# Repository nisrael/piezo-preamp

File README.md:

# piezo-preamp

This is a piezo preamp with a gain boost and a variable high and low pass filter.
It is a modification of the DIY ilski PB-1 (https://breaksberlin.wordpress.com/2015/11/07/diy-piezo-preamp-with-hi-pass-filter/).

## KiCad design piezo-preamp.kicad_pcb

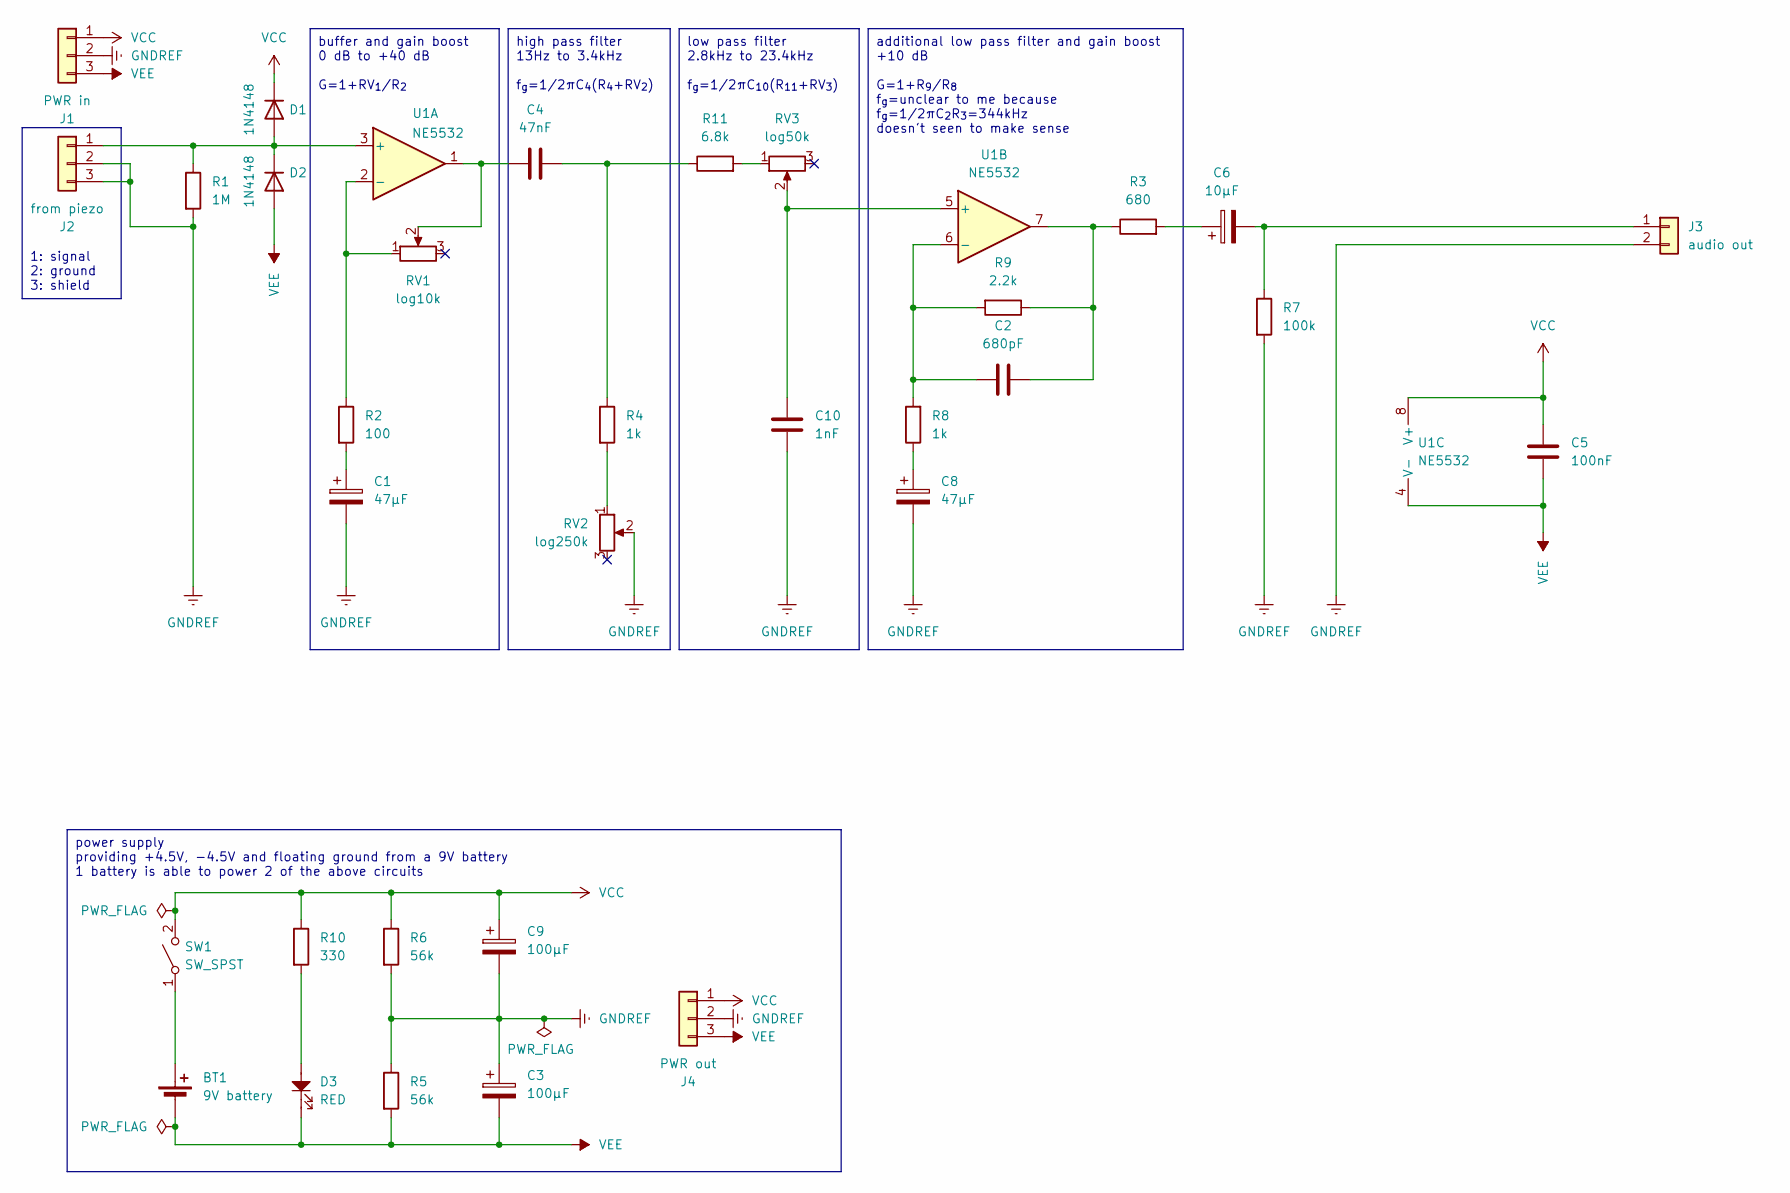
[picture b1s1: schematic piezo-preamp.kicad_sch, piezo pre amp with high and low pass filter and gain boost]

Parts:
BT1: 9V battery; PinHeader_1x02_P2.54mm_Vertical
C1, C8: 47µF; CP_Radial_D5.0mm_P2.50mm
C2: 680pF; CP_Radial_D5.0mm_P2.50mm
C3, C9: 100µF; CP_Radial_D5.0mm_P2.50mm
C4: 47nF; CP_Radial_D5.0mm_P2.50mm
C5: 100nF; CP_Radial_D5.0mm_P2.50mm
C6: 10µF; CP_Radial_D5.0mm_P2.50mm
C10: 1nF; CP_Radial_D5.0mm_P2.50mm
D1, D2: 1N4148; D_A-405_P7.62mm_Horizontal
D3: RED; LED_D5.0mm
J1: PWR in; PinHeader_1x03_P2.54mm_Vertical
J2: from piezo; PinHeader_1x03_P2.54mm_Vertical
J3: audio out; PinHeader_1x02_P2.54mm_Vertical
J4: PWR out; PinHeader_1x03_P2.54mm_Vertical
R1: 1M; R_Axial_DIN0207_L6.3mm_D2.5mm_P10.16mm_Horizontal
R2: 100; R_Axial_DIN0207_L6.3mm_D2.5mm_P10.16mm_Horizontal
R3: 680; R_Axial_DIN0207_L6.3mm_D2.5mm_P10.16mm_Horizontal
R4, R8: 1k; R_Axial_DIN0207_L6.3mm_D2.5mm_P10.16mm_Horizontal
R5, R6: 56k; R_Axial_DIN0207_L6.3mm_D2.5mm_P10.16mm_Horizontal
R7: 100k; R_Axial_DIN0207_L6.3mm_D2.5mm_P10.16mm_Horizontal
R9: 2.2k; R_Axial_DIN0207_L6.3mm_D2.5mm_P10.16mm_Horizontal
R10: 330; R_Axial_DIN0207_L6.3mm_D2.5mm_P10.16mm_Horizontal
R11: 6.8k; R_Axial_DIN0207_L6.3mm_D2.5mm_P10.16mm_Horizontal
RV1: log10k; PinHeader_1x02_P2.54mm_Vertical
RV2: log250k; PinHeader_1x02_P2.54mm_Vertical
RV3: log50k; PinHeader_1x02_P2.54mm_Vertical
SW1: SW_SPST; PinHeader_1x02_P2.54mm_Vertical
U1: NE5532; CERDIP-8_W7.62mm_SideBrazed_Socket

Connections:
GNDREF: C1.2, C3.1, C8.2, C9.2, C10.1, J1.2, J2.2, J2.3, J3.2, J4.2, R1.2, R5.1, R6.2, R7.2, RV2.2
unnamed: BT1.1 (+), SW1.1 (A)
unnamed: C1.1, R2.2
unnamed: C2.1, R3.1, R9.1, U1.7
unnamed: C4.1, RV1.2, U1.1
unnamed: C4.2, R4.1, R11.1
unnamed: C6.1, R3.2
unnamed: C8.1, R8.1
unnamed: D1.2 (A), D2.1 (K), J2.1, R1.1, U1.3 (+)
unnamed: D3.2, R10.2
unnamed: C6.2, J3.1, R7.1
unnamed: R4.2, RV2.1
unnamed: R11.2, RV3.1
unnamed: R2.1, RV1.1, U1.2 (-)
unnamed: C10.2, RV3.2, U1.5 (+)
unnamed: C2.2, R8.2, R9.2, U1.6 (-)
VCC: C5.1, C9.1, D1.1 (K), J1.1, J4.1, R6.1, R10.1, SW1.2 (B), U1.8 (V+)
VEE: BT1.2 (-), C3.2, C5.2, D2.2 (A), D3.1, J1.3, J4.3, R5.2, U1.4 (V-)

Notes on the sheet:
buffer and gain boost 0 dB to +40 dB G=1+RV_{1}/R_{2}
high pass filter 13Hz to 3.4kHz f_{g}=1/2πC_{4}(R_{4}+RV_{2})
low pass filter 2.8kHz to 23.4kHz f_{g}=1/2πC_{10}(R_{11}+RV_{3})
additional low pass filter and gain boost +10 dB G=1+R_{9}/R_{8} f_{g}=unclear to me because f_{g}=1/2πC_{2}R_{3}=344kHz doesn't seen to make sense
1: signal 2: ground 3: shield
power supply providing +4.5V, -4.5V and floating ground from a 9V battery 1 battery is able to power 2 of the above circuits

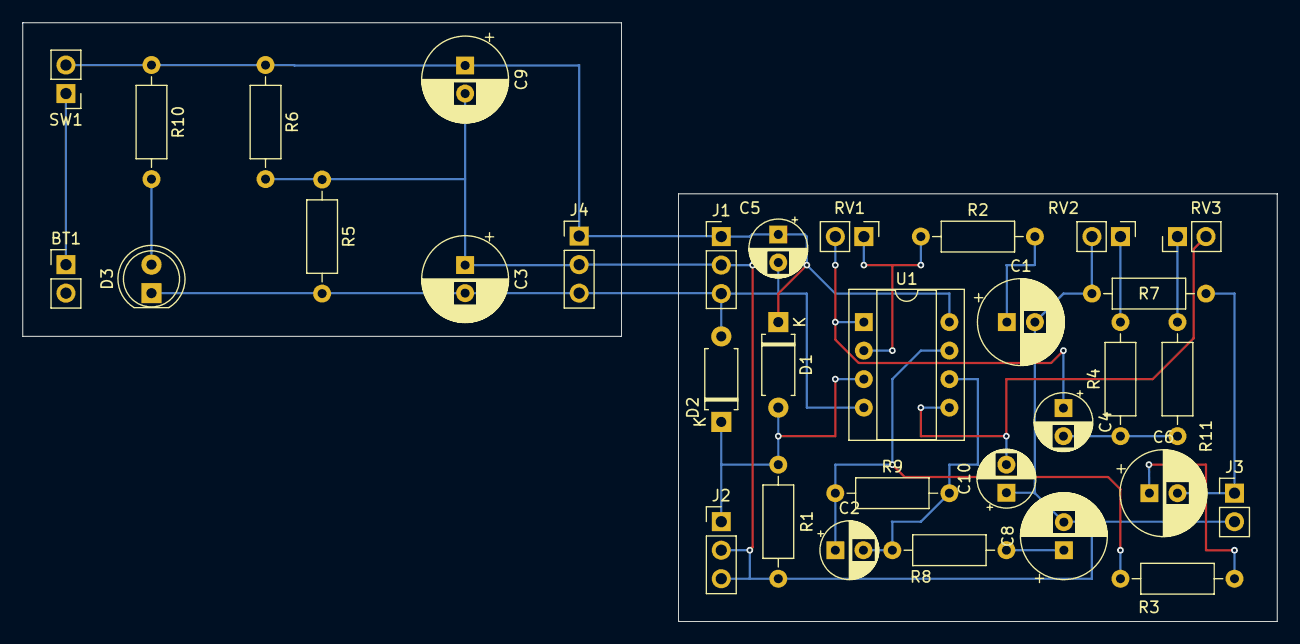
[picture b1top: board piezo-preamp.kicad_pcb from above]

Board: 2 copper layers, 111.8 x 53.3 mm, 33 parts (0 on the bottom side), 18 nets.
